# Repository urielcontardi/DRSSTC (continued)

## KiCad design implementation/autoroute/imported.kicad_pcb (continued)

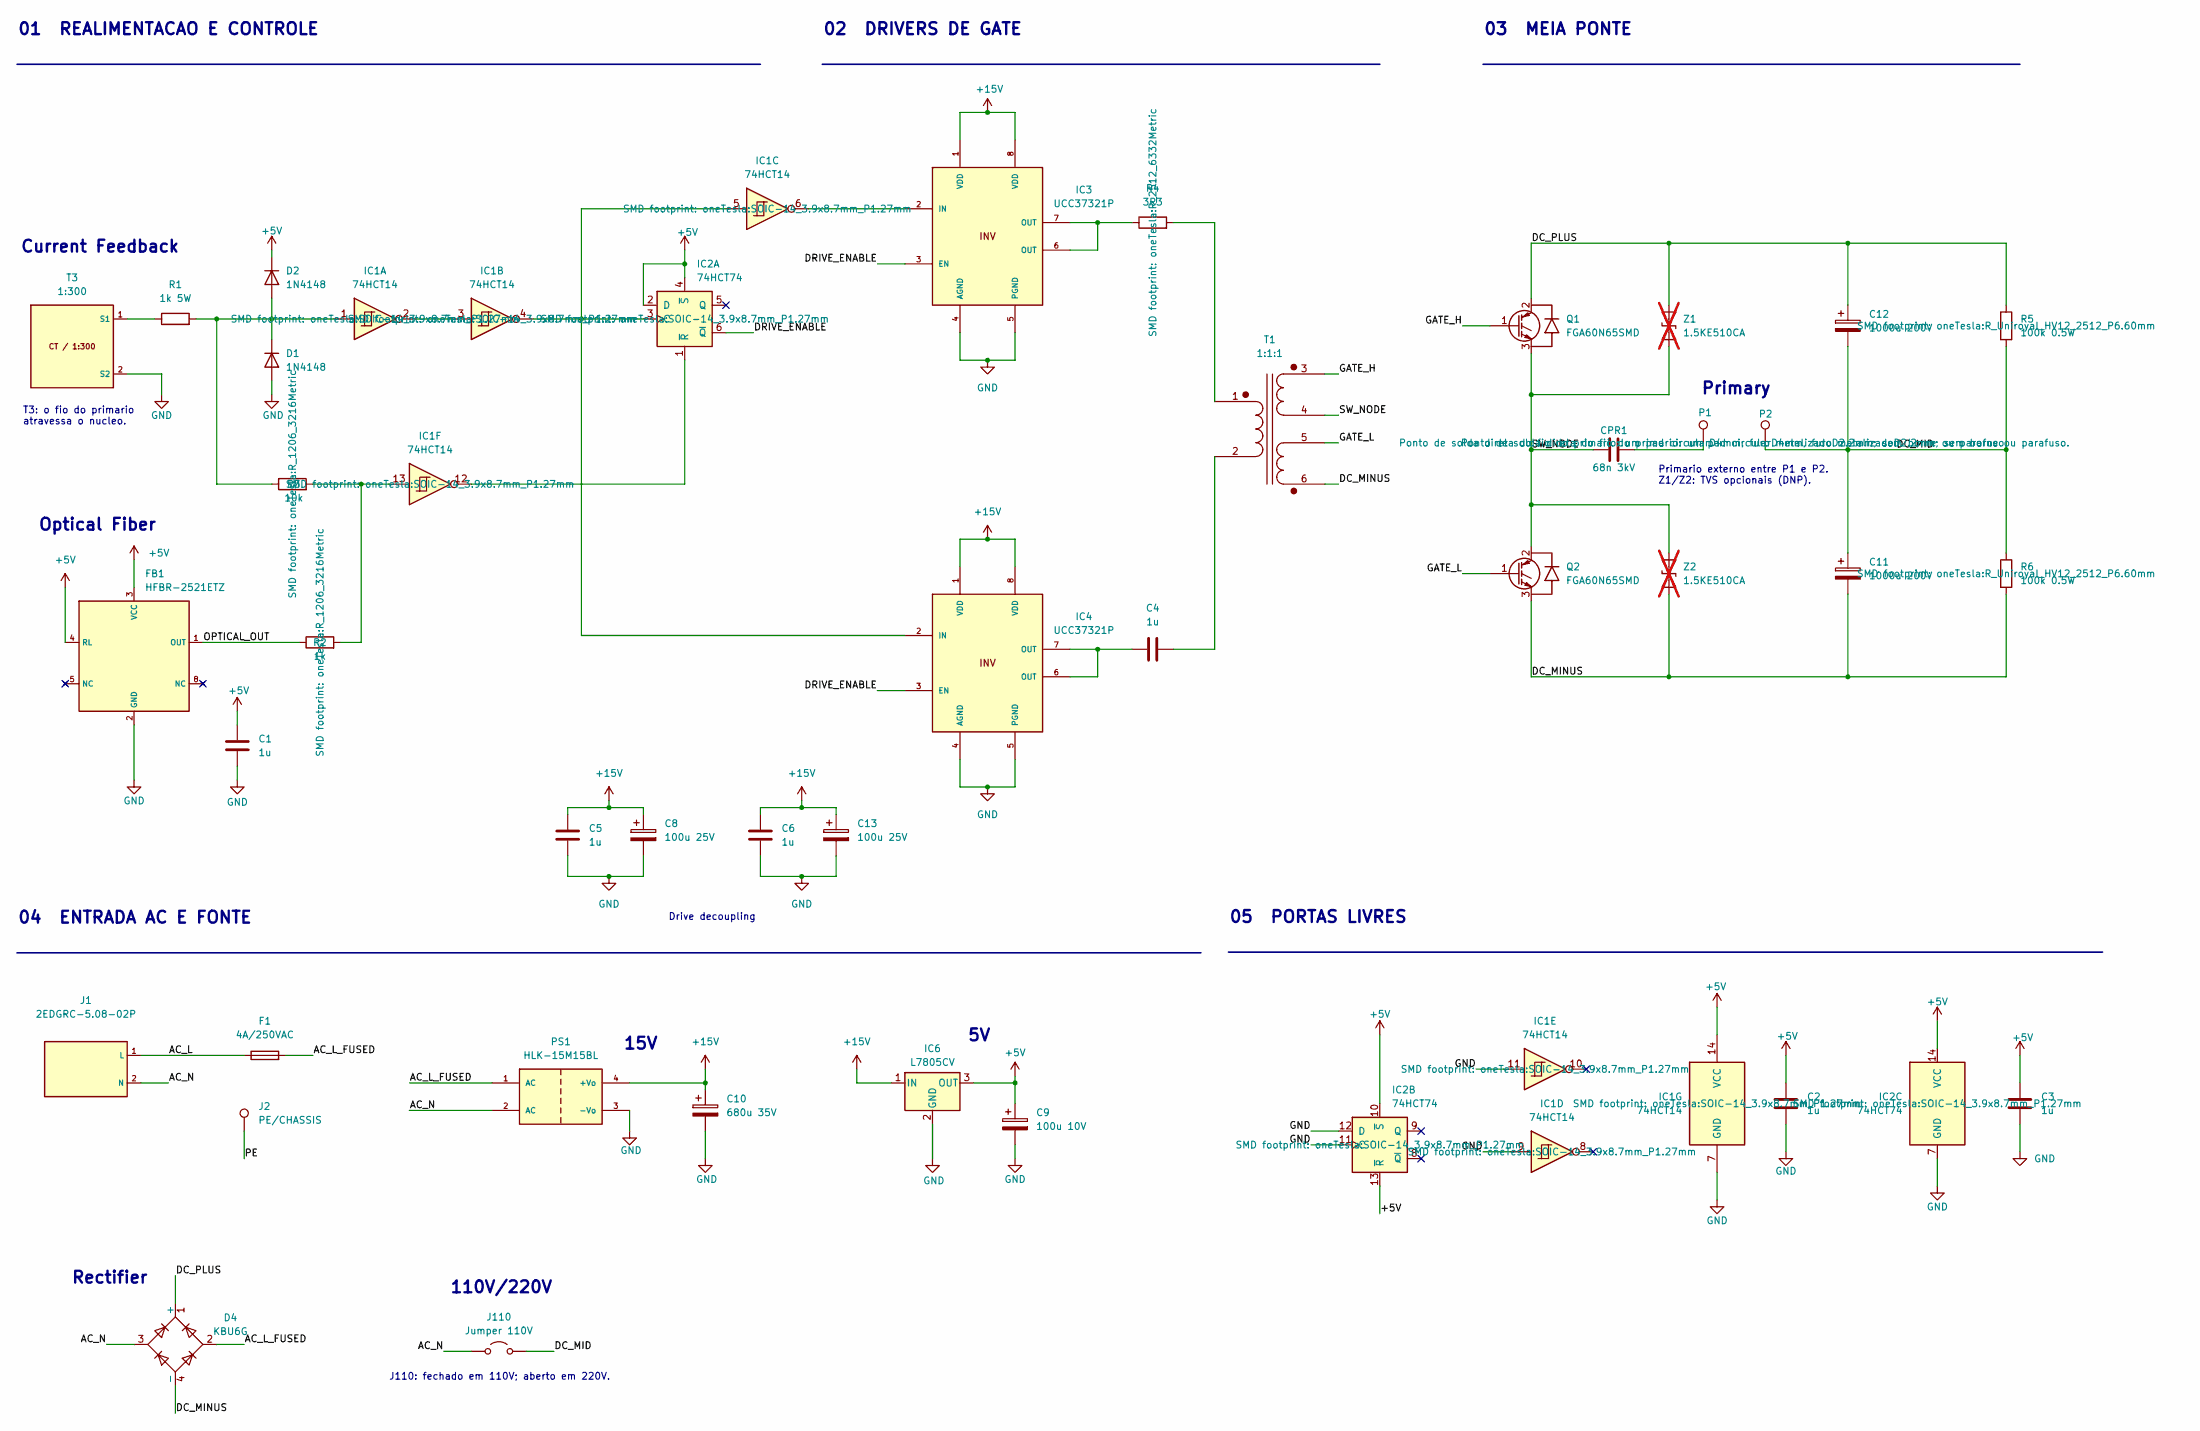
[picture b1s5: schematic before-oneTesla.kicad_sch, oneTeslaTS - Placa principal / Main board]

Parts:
C1, C2, C3, C4, C5, C6: 1u; C_Disc_D7.5mm_W2.5mm_P5.00mm
C8, C13: 100u 25V; CP_D8_P2.54_ReviewPending
C9: 100u 10V; CP_D8_P2.54_ReviewPending
C10: 680u 35V; CP_D12.5_P3.556_ReviewPending
C11, C12: 1000u 200V; CP_D30_P10.16_ReviewPending
CPR1: 68n 3kV; CDE_940C30S68K_F_CONFIRMAR
D1, D2: 1N4148; D_DO-35_SOD27_P7.62mm_Horizontal
D4: KBU6G; Diode_Bridge_Vishay_KBU
F1: 4A/250VAC; Fuseholder_Idall_AS-06_5x20mm_P20.20mm_Horizontal
FB1: HFBR-2521ETZ
IC1: 74HCT14; SOIC-14_3.9x8.7mm_P1.27mm
IC2: 74HCT74; SOIC-14_3.9x8.7mm_P1.27mm
IC3, IC4: UCC37321P; DIP-8_W7.62mm_Socket_LongPads
IC6: L7805CV; TO-220-3_Vertical
J1: 2EDGRC-5.08-02P; TerminalBlock_2EDGRC-5.08_1x02_P5.08mm_Horizontal
J2: PE/CHASSIS; Chassis_PE_M3
J110: Jumper 110V; J110_WireLink_P10.16mm
P1: PRIMARIO A; Primary_WirePad_D4.0mm_Drill2.2mm
P2: PRIMARIO B; Primary_WirePad_D4.0mm_Drill2.2mm
PS1: HLK-15M15BL
Q1, Q2: FGA60N65SMD; Q_TO3P_ImportedPads_ReviewPending
R1: 1k 5W; R_Bourns_PWR8030_20.8x7.6mm_P17.80mm
R2: 1k; R_1206_3216Metric
R3: 10k; R_1206_3216Metric
R4: 3R3; R_2512_6332Metric
R5, R6: 100k 0.5W; R_Uniroyal_HV12_2512_P6.60mm
T1: 1:1:1; GDT_6Pin_CONFIRMAR
T3: 1:300; CT_1_300_P12.70mm_CONFIRMAR
Z1, Z2: 1.5KE510CA; D_DO201AD_P14.732_ReviewPending; not fitted

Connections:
+5V: C1.1, C2.1, C3.1, C9.1, D2.1 (K), FB1.3 (VCC), FB1.4 (RL), IC1.14 (VCC), IC2.2 (D), IC2.4 (~S), IC2.10 (~S), IC2.13 (~R), IC2.14 (VCC), IC6.3 (OUT)
+15V: C5.1, C6.1, C8.1, C10.1, C13.1, IC3.1 (VDD), IC3.8 (VDD), IC4.1 (VDD), IC4.8 (VDD), IC6.1 (IN), PS1.4 (+Vo)
/AC_L: F1.1, J1.1 (L)
/AC_L_FUSED: D4.2, F1.2, PS1.1 (AC)
/AC_N: D4.3, J1.2 (N), J110.1 (A), PS1.2 (AC)
/DC_MID: C11.1, C12.2, J110.2 (B), P2.1 (1_1), R5.2, R6.1
/DC_MINUS: C11.2, D4.4 (-), Q2.3 (E), R6.2, T1.6 (SD), Z2.2 (A2)
/DC_PLUS: C12.1, D4.1 (+), Q1.2 (C), R5.1, Z1.1 (A1)
/DRIVE_ENABLE: IC2.6 (~Q), IC3.3 (EN), IC4.3 (EN)
/GATE_H: Q1.1 (G), T1.3 (SA)
/GATE_L: Q2.1 (G), T1.5 (SC)
/OPTICAL_OUT: FB1.1 (OUT), R2.1
GND: C1.2, C2.2, C3.2, C5.2, C6.2, C8.2, C9.2, C10.2, C13.2, D1.2 (A), FB1.2 (GND), IC1.7 (GND), IC1.9, IC1.11, IC2.7 (GND), IC2.11 (C), IC2.12 (D), IC3.4 (AGND), IC3.5 (PGND), IC4.4 (AGND), IC4.5 (PGND), IC6.2 (GND), J2.1, PS1.3 (-Vo), T3.2 (S2)
unnamed: C4.1, IC4.6 (OUT), IC4.7 (OUT)
unnamed: CPR1.2, P1.1 (1_1)
unnamed: D1.1 (K), D2.2 (A), IC1.1, R1.2, R3.1
unnamed: IC1.2, IC1.3
unnamed: IC1.13, R2.2, R3.2
unnamed: IC1.4, IC1.5, IC2.3 (C), IC4.2 (IN)
unnamed: IC1.12, IC2.1 (~R)
unnamed: IC1.6, IC3.2 (IN)
unnamed: IC3.6 (OUT), IC3.7 (OUT), R4.1
unnamed: R4.2, T1.1 (AA)
unnamed: C4.2, T1.2 (AB)
unnamed: R1.1, T3.1 (S1)

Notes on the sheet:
110V/220V
01 REALIMENTACAO E CONTROLE
03 MEIA PONTE
T3: o fio do primario atravessa o nucleo.
J110: fechado em 110V; aberto em 220V.
04 ENTRADA AC E FONTE
Drive decoupling
Current Feedback
Rectifier
Primario externo entre P1 e P2. Z1/Z2: TVS opcionais (DNP).
15V
02 DRIVERS DE GATE
05 PORTAS LIVRES
Optical Fiber
Primary

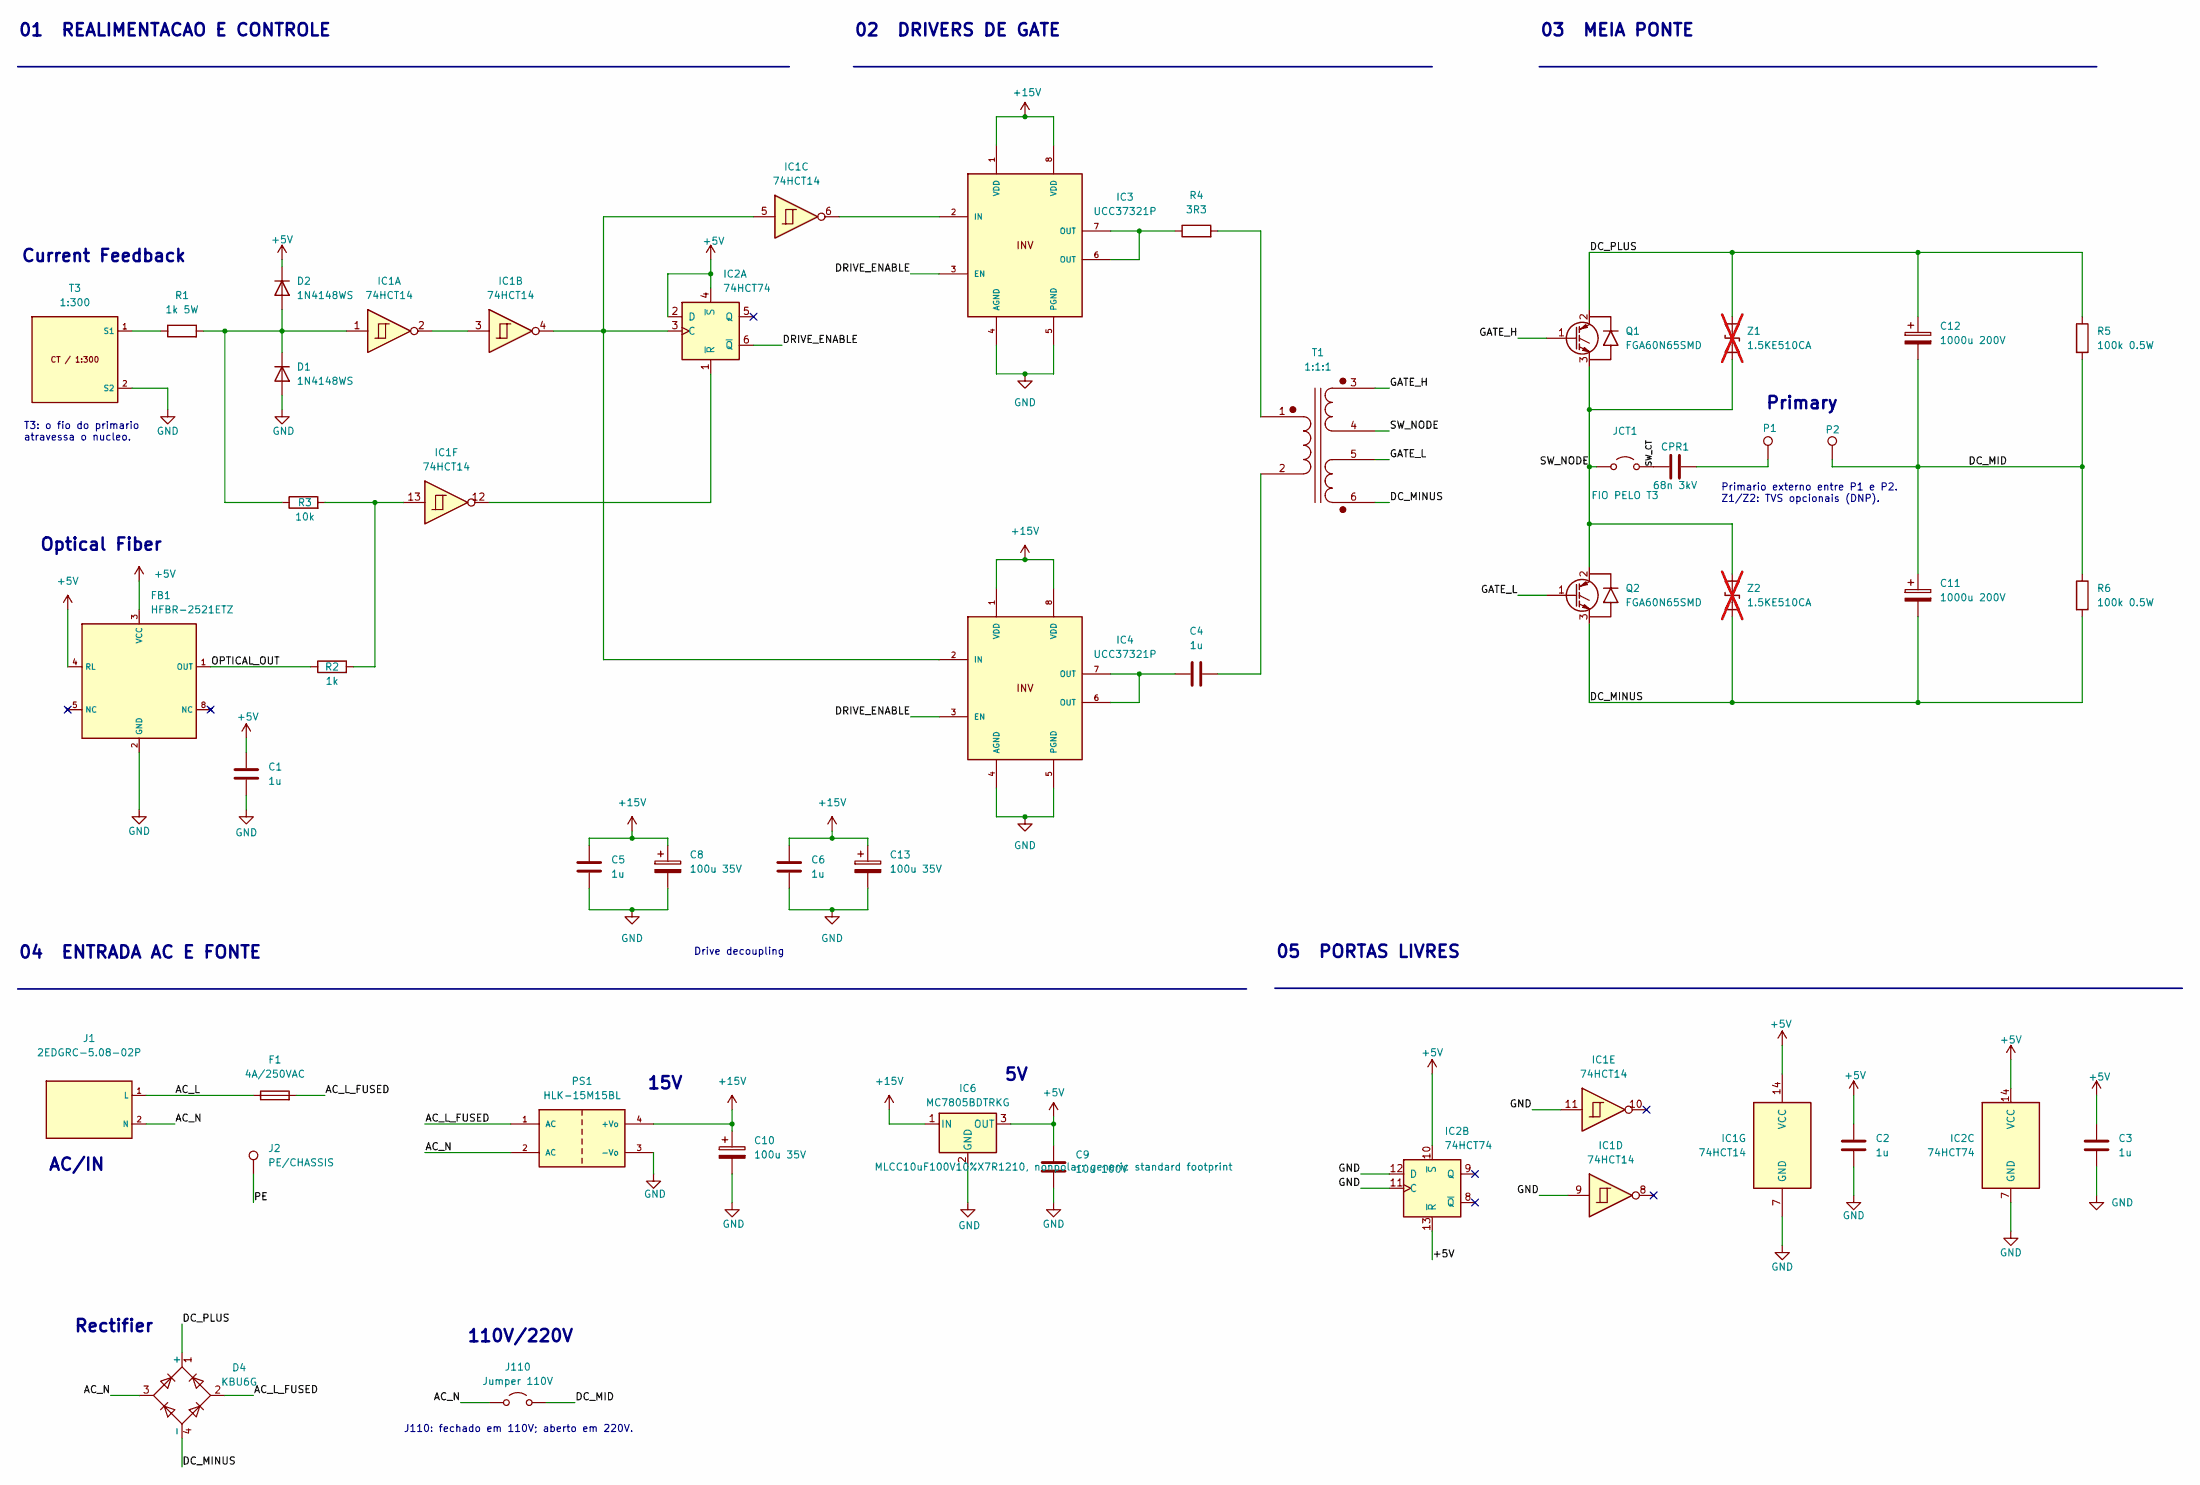
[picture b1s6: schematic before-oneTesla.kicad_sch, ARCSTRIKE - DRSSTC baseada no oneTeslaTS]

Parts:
C1, C2, C3, C5, C6: 1u; C_0805_2012Metric_Pad1.18x1.45mm_HandSolder
C4: 1u; C_Disc_D7.5mm_W2.5mm_P5.00mm
C8, C10, C13: 100u 35V; CP_Elec_8x10
C9: 10u 100V; C_1210_3225Metric
C11, C12: 1000u 200V; CP_D25_H45_P10.16_ReviewPending
CPR1: 68n 3kV; CDE_940C30S68K_F_CONFIRMAR
D1, D2: 1N4148WS; D_SOD-323_HandSoldering
D4: KBU6G; Diode_Bridge_Vishay_KBU
F1: 4A/250VAC; Fuseholder_Idall_AS-06_5x20mm_Slotted_P22.35mm
FB1: HFBR-2521ETZ
IC1: 74HCT14; SOIC-14_3.9x8.7mm_P1.27mm
IC2: 74HCT74; SOIC-14_3.9x8.7mm_P1.27mm
IC3, IC4: UCC37321P; DIP-8_W7.62mm_Socket_LongPads
IC6: MC7805BDTRKG; TO-252-3_TabPin2
J1: 2EDGRC-5.08-02P; TerminalBlock_2EDGRC-5.08_1x02_P5.08mm_Horizontal
J2: PE/CHASSIS; Chassis_PE_M3
J110: Jumper 110V; J110_WireLink_P15.24mm
JCT1: FIO PELO T3; CT_Primary_WireLink_P21.59mm
P1: PRIMARIO A; Primary_WirePad_D4.0mm_Drill2.2mm
P2: PRIMARIO B; Primary_WirePad_D4.0mm_Drill2.2mm
PS1: HLK-15M15BL
Q1, Q2: FGA60N65SMD; Q_TO3P_ImportedPads_ReviewPending
R1: 1k 5W; R_Axial_Vishay_AC05_L18.0mm_D7.5mm_P10.16mm_Vertical
R2: 1k; R_1206_3216Metric
R3: 10k; R_1206_3216Metric
R4: 3R3; R_Axial_DIN0207_L6.3mm_D2.5mm_P7.62mm_Horizontal
R5, R6: 100k 0.5W; R_Uniroyal_HV12_2512_P6.60mm
T1: 1:1:1; GDT_6Pin_CONFIRMAR
T3: 1:300; CT_1_300_P12.70mm_CONFIRMAR
Z1, Z2: 1.5KE510CA; D_DO201AD_P14.732_ReviewPending; not fitted

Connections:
+5V: C1.1, C2.1, C3.1, C9.1, D2.1 (K), FB1.3 (VCC), FB1.4 (RL), IC1.14 (VCC), IC2.2 (D), IC2.4 (~S), IC2.10 (~S), IC2.13 (~R), IC2.14 (VCC), IC6.3 (OUT)
+15V: C5.1, C6.1, C8.1, C10.1, C13.1, IC3.1 (VDD), IC3.8 (VDD), IC4.1 (VDD), IC4.8 (VDD), IC6.1 (IN), PS1.4 (+Vo)
/AC_L: F1.1, J1.1 (L)
/AC_L_FUSED: D4.2, F1.2, PS1.1 (AC)
/AC_N: D4.3, J1.2 (N), J110.1 (A), PS1.2 (AC)
/DC_MID: C11.1, C12.2, J110.2 (B), P2.1 (1_1), R5.2, R6.1
/DC_MINUS: C11.2, D4.4 (-), Q2.3 (E), R6.2, T1.6 (SD), Z2.2 (A2)
/DC_PLUS: C12.1, D4.1 (+), Q1.2 (C), R5.1, Z1.1 (A1)
/DRIVE_ENABLE: IC2.6 (~Q), IC3.3 (EN), IC4.3 (EN)
/GATE_H: Q1.1 (G), T1.3 (SA)
/GATE_L: Q2.1 (G), T1.5 (SC)
/OPTICAL_OUT: FB1.1 (OUT), R2.1
GND: C1.2, C2.2, C3.2, C5.2, C6.2, C8.2, C9.2, C10.2, C13.2, D1.2 (A), FB1.2 (GND), IC1.7 (GND), IC1.9, IC1.11, IC2.7 (GND), IC2.11 (C), IC2.12 (D), IC3.4 (AGND), IC3.5 (PGND), IC4.4 (AGND), IC4.5 (PGND), IC6.2 (GND), J2.1, PS1.3 (-Vo), T3.2 (S2)
unnamed: C4.1, IC4.6 (OUT), IC4.7 (OUT)
unnamed: CPR1.2, P1.1 (1_1)
unnamed: D1.1 (K), D2.2 (A), IC1.1, R1.2, R3.1
unnamed: IC1.2, IC1.3
unnamed: IC1.13, R2.2, R3.2
unnamed: IC1.4, IC1.5, IC2.3 (C), IC4.2 (IN)
unnamed: IC1.12, IC2.1 (~R)
unnamed: IC1.6, IC3.2 (IN)
unnamed: IC3.6 (OUT), IC3.7 (OUT), R4.1
unnamed: R4.2, T1.1 (AA)
unnamed: C4.2, T1.2 (AB)
unnamed: R1.1, T3.1 (S1)

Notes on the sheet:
110V/220V
01 REALIMENTACAO E CONTROLE
03 MEIA PONTE
T3: o fio do primario atravessa o nucleo.
J110: fechado em 110V; aberto em 220V.
04 ENTRADA AC E FONTE
Drive decoupling
Current Feedback
AC/IN
Rectifier
Primario externo entre P1 e P2. Z1/Z2: TVS opcionais (DNP).
15V
02 DRIVERS DE GATE
05 PORTAS LIVRES
Optical Fiber
Primary

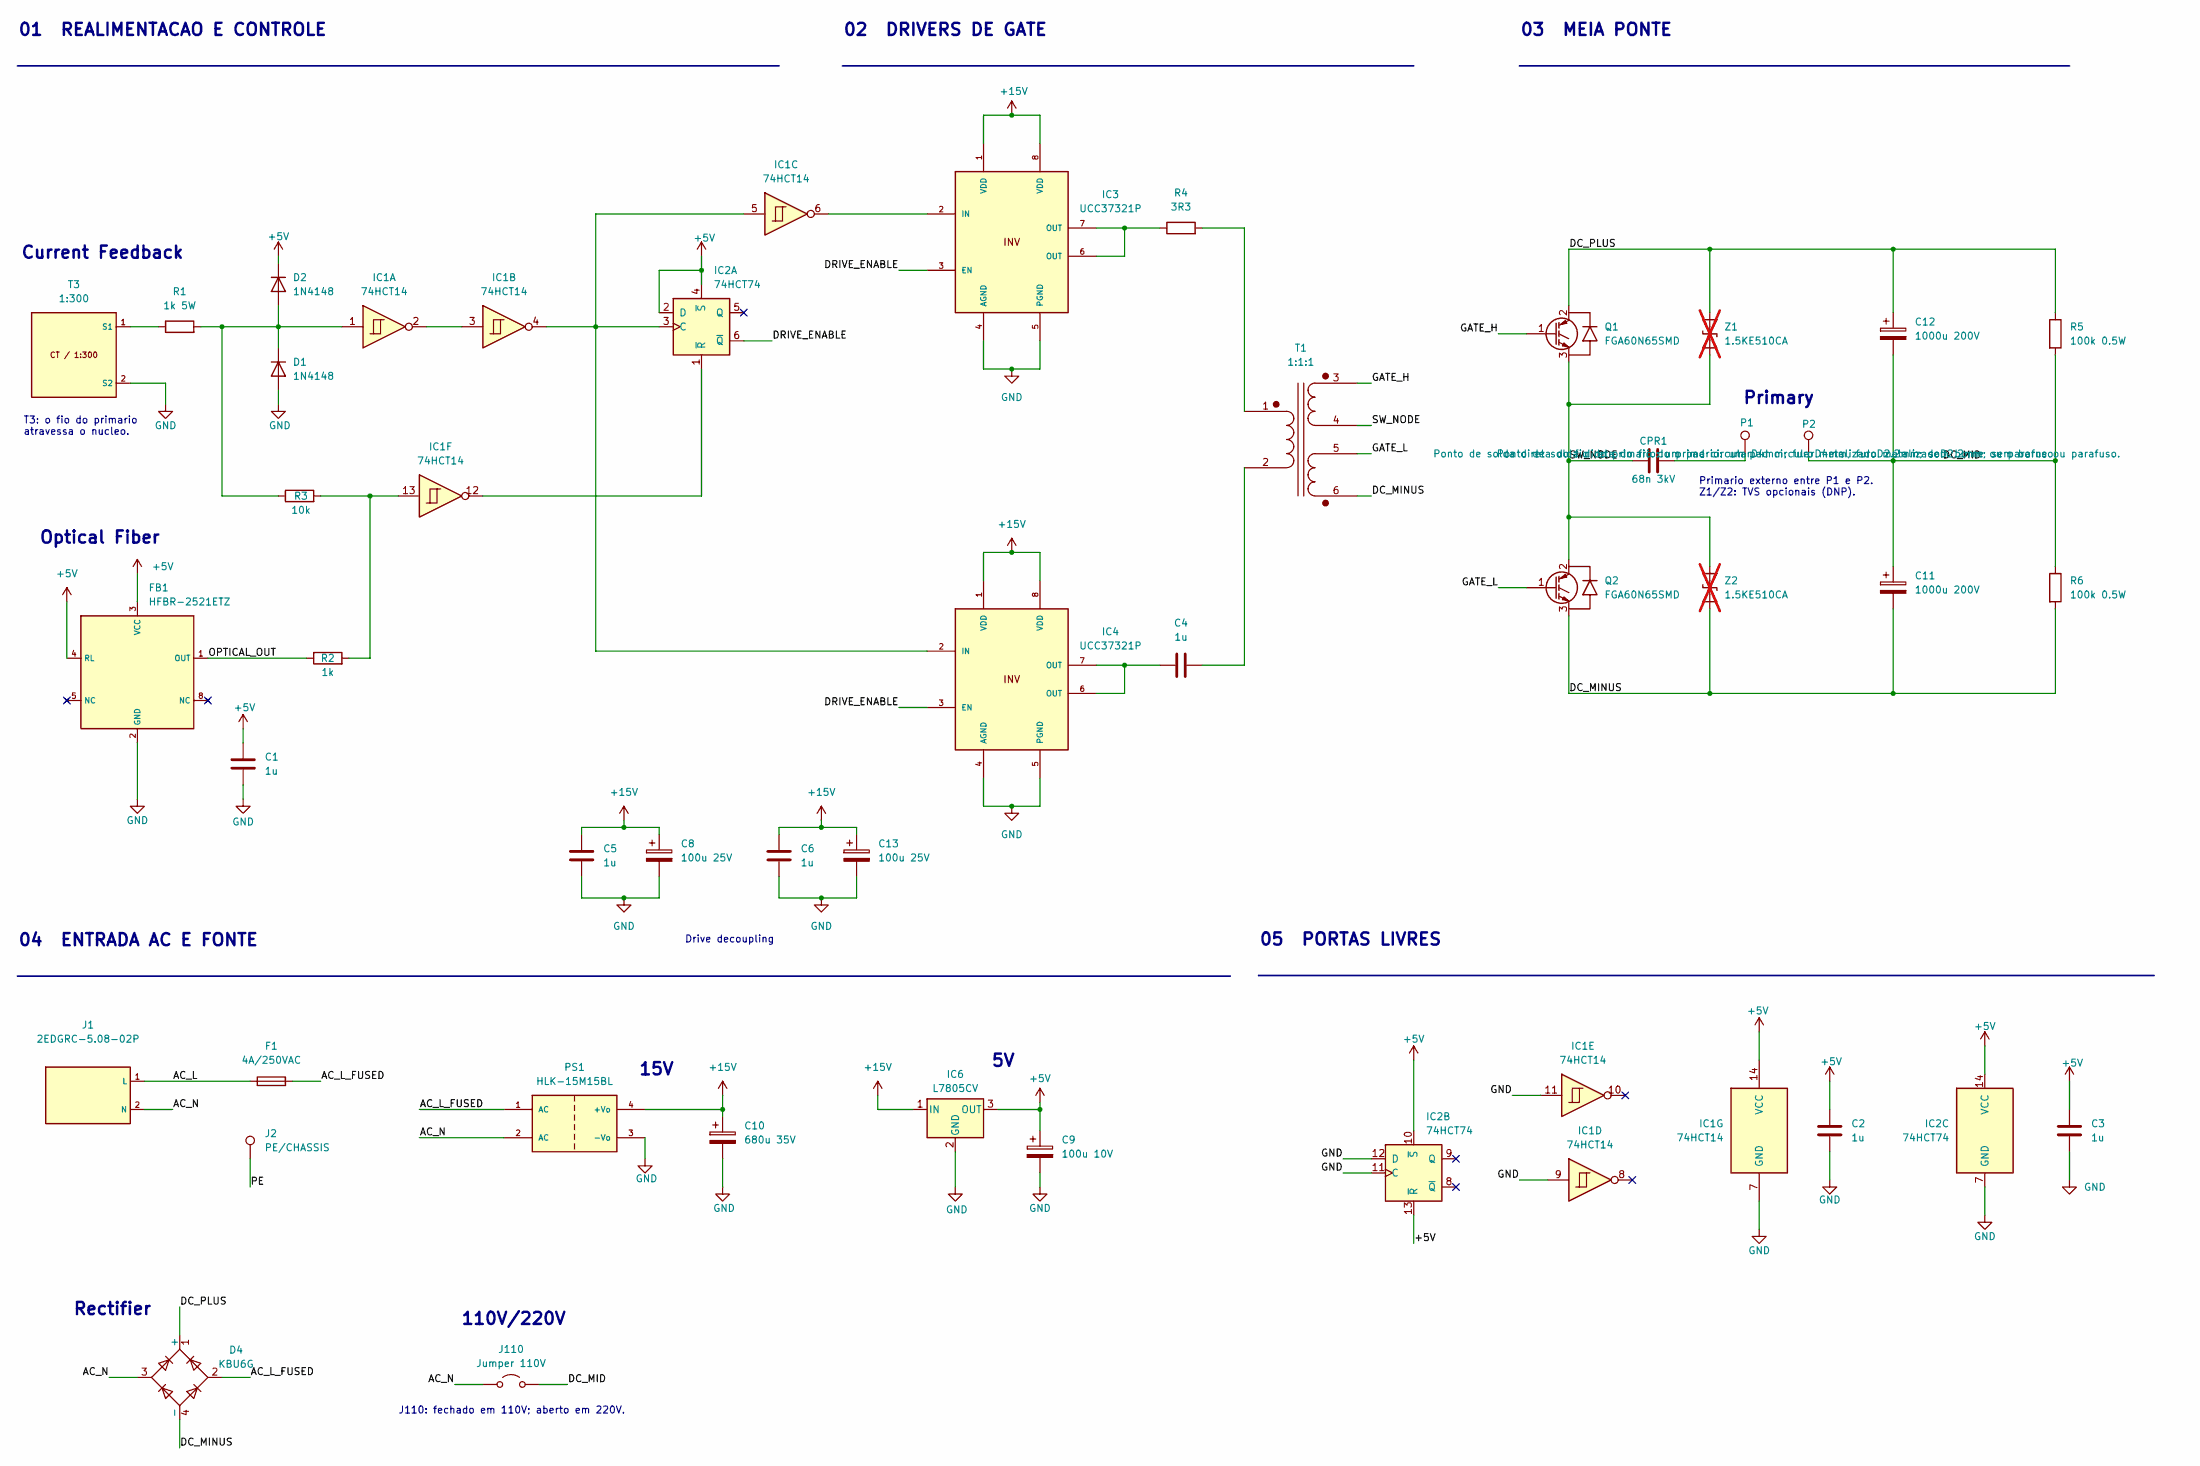
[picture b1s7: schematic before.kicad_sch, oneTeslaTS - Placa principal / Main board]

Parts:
C1, C2, C3, C4, C5, C6: 1u; C_Disc_D7.5mm_W2.5mm_P5.00mm
C8, C13: 100u 25V; CP_D8_P2.54_ReviewPending
C9: 100u 10V; CP_D8_P2.54_ReviewPending
C10: 680u 35V; CP_D12.5_P3.556_ReviewPending
C11, C12: 1000u 200V; CP_D30_P10.16_ReviewPending
CPR1: 68n 3kV; CDE_940C30S68K_F_CONFIRMAR
D1, D2: 1N4148; D_DO-35_SOD27_P7.62mm_Horizontal
D4: KBU6G; Diode_Bridge_Vishay_KBU
F1: 4A/250VAC; Fuseholder_Idall_AS-06_5x20mm_P20.20mm_Horizontal
FB1: HFBR-2521ETZ
IC1: 74HCT14; DIP-14_W7.62mm_Socket_LongPads
IC2: 74HCT74; DIP-14_W7.62mm_Socket_LongPads
IC3, IC4: UCC37321P; DIP-8_W7.62mm_Socket_LongPads
IC6: L7805CV; TO-220-3_Vertical
J1: 2EDGRC-5.08-02P; TerminalBlock_2EDGRC-5.08_1x02_P5.08mm_Horizontal
J2: PE/CHASSIS; Chassis_PE_M3
J110: Jumper 110V; J110_WireLink_P10.16mm
P1: PRIMARIO A; Primary_WirePad_D4.0mm_Drill2.2mm
P2: PRIMARIO B; Primary_WirePad_D4.0mm_Drill2.2mm
PS1: HLK-15M15BL
Q1, Q2: FGA60N65SMD; Q_TO3P_ImportedPads_ReviewPending
R1: 1k 5W; R_Axial_Vishay_AC05_L18.0mm_D7.5mm_P23.40mm_Horizontal
R2: 1k; R_Axial_DIN0207_L6.3mm_D2.5mm_P7.62mm_Horizontal
R3: 10k; R_Axial_DIN0207_L6.3mm_D2.5mm_P7.62mm_Horizontal
R4: 3R3; R_Axial_DIN0207_L6.3mm_D2.5mm_P7.62mm_Horizontal
R5, R6: 100k 0.5W; R_L9_P10.16_ReviewPending
T1: 1:1:1; GDT_6Pin_CONFIRMAR
T3: 1:300; CT_1_300_P12.70mm_CONFIRMAR
Z1, Z2: 1.5KE510CA; D_DO201AD_P14.732_ReviewPending; not fitted

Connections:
+5V: C1.1, C2.1, C3.1, C9.1, D2.1 (K), FB1.3 (VCC), FB1.4 (RL), IC1.14 (VCC), IC2.2 (D), IC2.4 (~S), IC2.10 (~S), IC2.13 (~R), IC2.14 (VCC), IC6.3 (OUT)
+15V: C5.1, C6.1, C8.1, C10.1, C13.1, IC3.1 (VDD), IC3.8 (VDD), IC4.1 (VDD), IC4.8 (VDD), IC6.1 (IN), PS1.4 (+Vo)
/AC_L: F1.1, J1.1 (L)
/AC_L_FUSED: D4.2, F1.2, PS1.1 (AC)
/AC_N: D4.3, J1.2 (N), J110.1 (A), PS1.2 (AC)
/DC_MID: C11.1, C12.2, J110.2 (B), P2.1 (1_1), R5.2, R6.1
/DC_MINUS: C11.2, D4.4 (-), Q2.3 (E), R6.2, T1.6 (SD), Z2.2 (A2)
/DC_PLUS: C12.1, D4.1 (+), Q1.2 (C), R5.1, Z1.1 (A1)
/DRIVE_ENABLE: IC2.6 (~Q), IC3.3 (EN), IC4.3 (EN)
/GATE_H: Q1.1 (G), T1.3 (SA)
/GATE_L: Q2.1 (G), T1.5 (SC)
/OPTICAL_OUT: FB1.1 (OUT), R2.1
GND: C1.2, C2.2, C3.2, C5.2, C6.2, C8.2, C9.2, C10.2, C13.2, D1.2 (A), FB1.2 (GND), IC1.7 (GND), IC1.9, IC1.11, IC2.7 (GND), IC2.11 (C), IC2.12 (D), IC3.4 (AGND), IC3.5 (PGND), IC4.4 (AGND), IC4.5 (PGND), IC6.2 (GND), J2.1, PS1.3 (-Vo), T3.2 (S2)
unnamed: C4.1, IC4.6 (OUT), IC4.7 (OUT)
unnamed: CPR1.2, P1.1 (1_1)
unnamed: D1.1 (K), D2.2 (A), IC1.1, R1.2, R3.1
unnamed: IC1.2, IC1.3
unnamed: IC1.13, R2.2, R3.2
unnamed: IC1.4, IC1.5, IC2.3 (C), IC4.2 (IN)
unnamed: IC1.12, IC2.1 (~R)
unnamed: IC1.6, IC3.2 (IN)
unnamed: IC3.6 (OUT), IC3.7 (OUT), R4.1
unnamed: R4.2, T1.1 (AA)
unnamed: C4.2, T1.2 (AB)
unnamed: R1.1, T3.1 (S1)

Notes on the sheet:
110V/220V
01 REALIMENTACAO E CONTROLE
03 MEIA PONTE
T3: o fio do primario atravessa o nucleo.
J110: fechado em 110V; aberto em 220V.
04 ENTRADA AC E FONTE
Drive decoupling
Current Feedback
Rectifier
Primario externo entre P1 e P2. Z1/Z2: TVS opcionais (DNP).
15V
02 DRIVERS DE GATE
05 PORTAS LIVRES
Optical Fiber
Primary

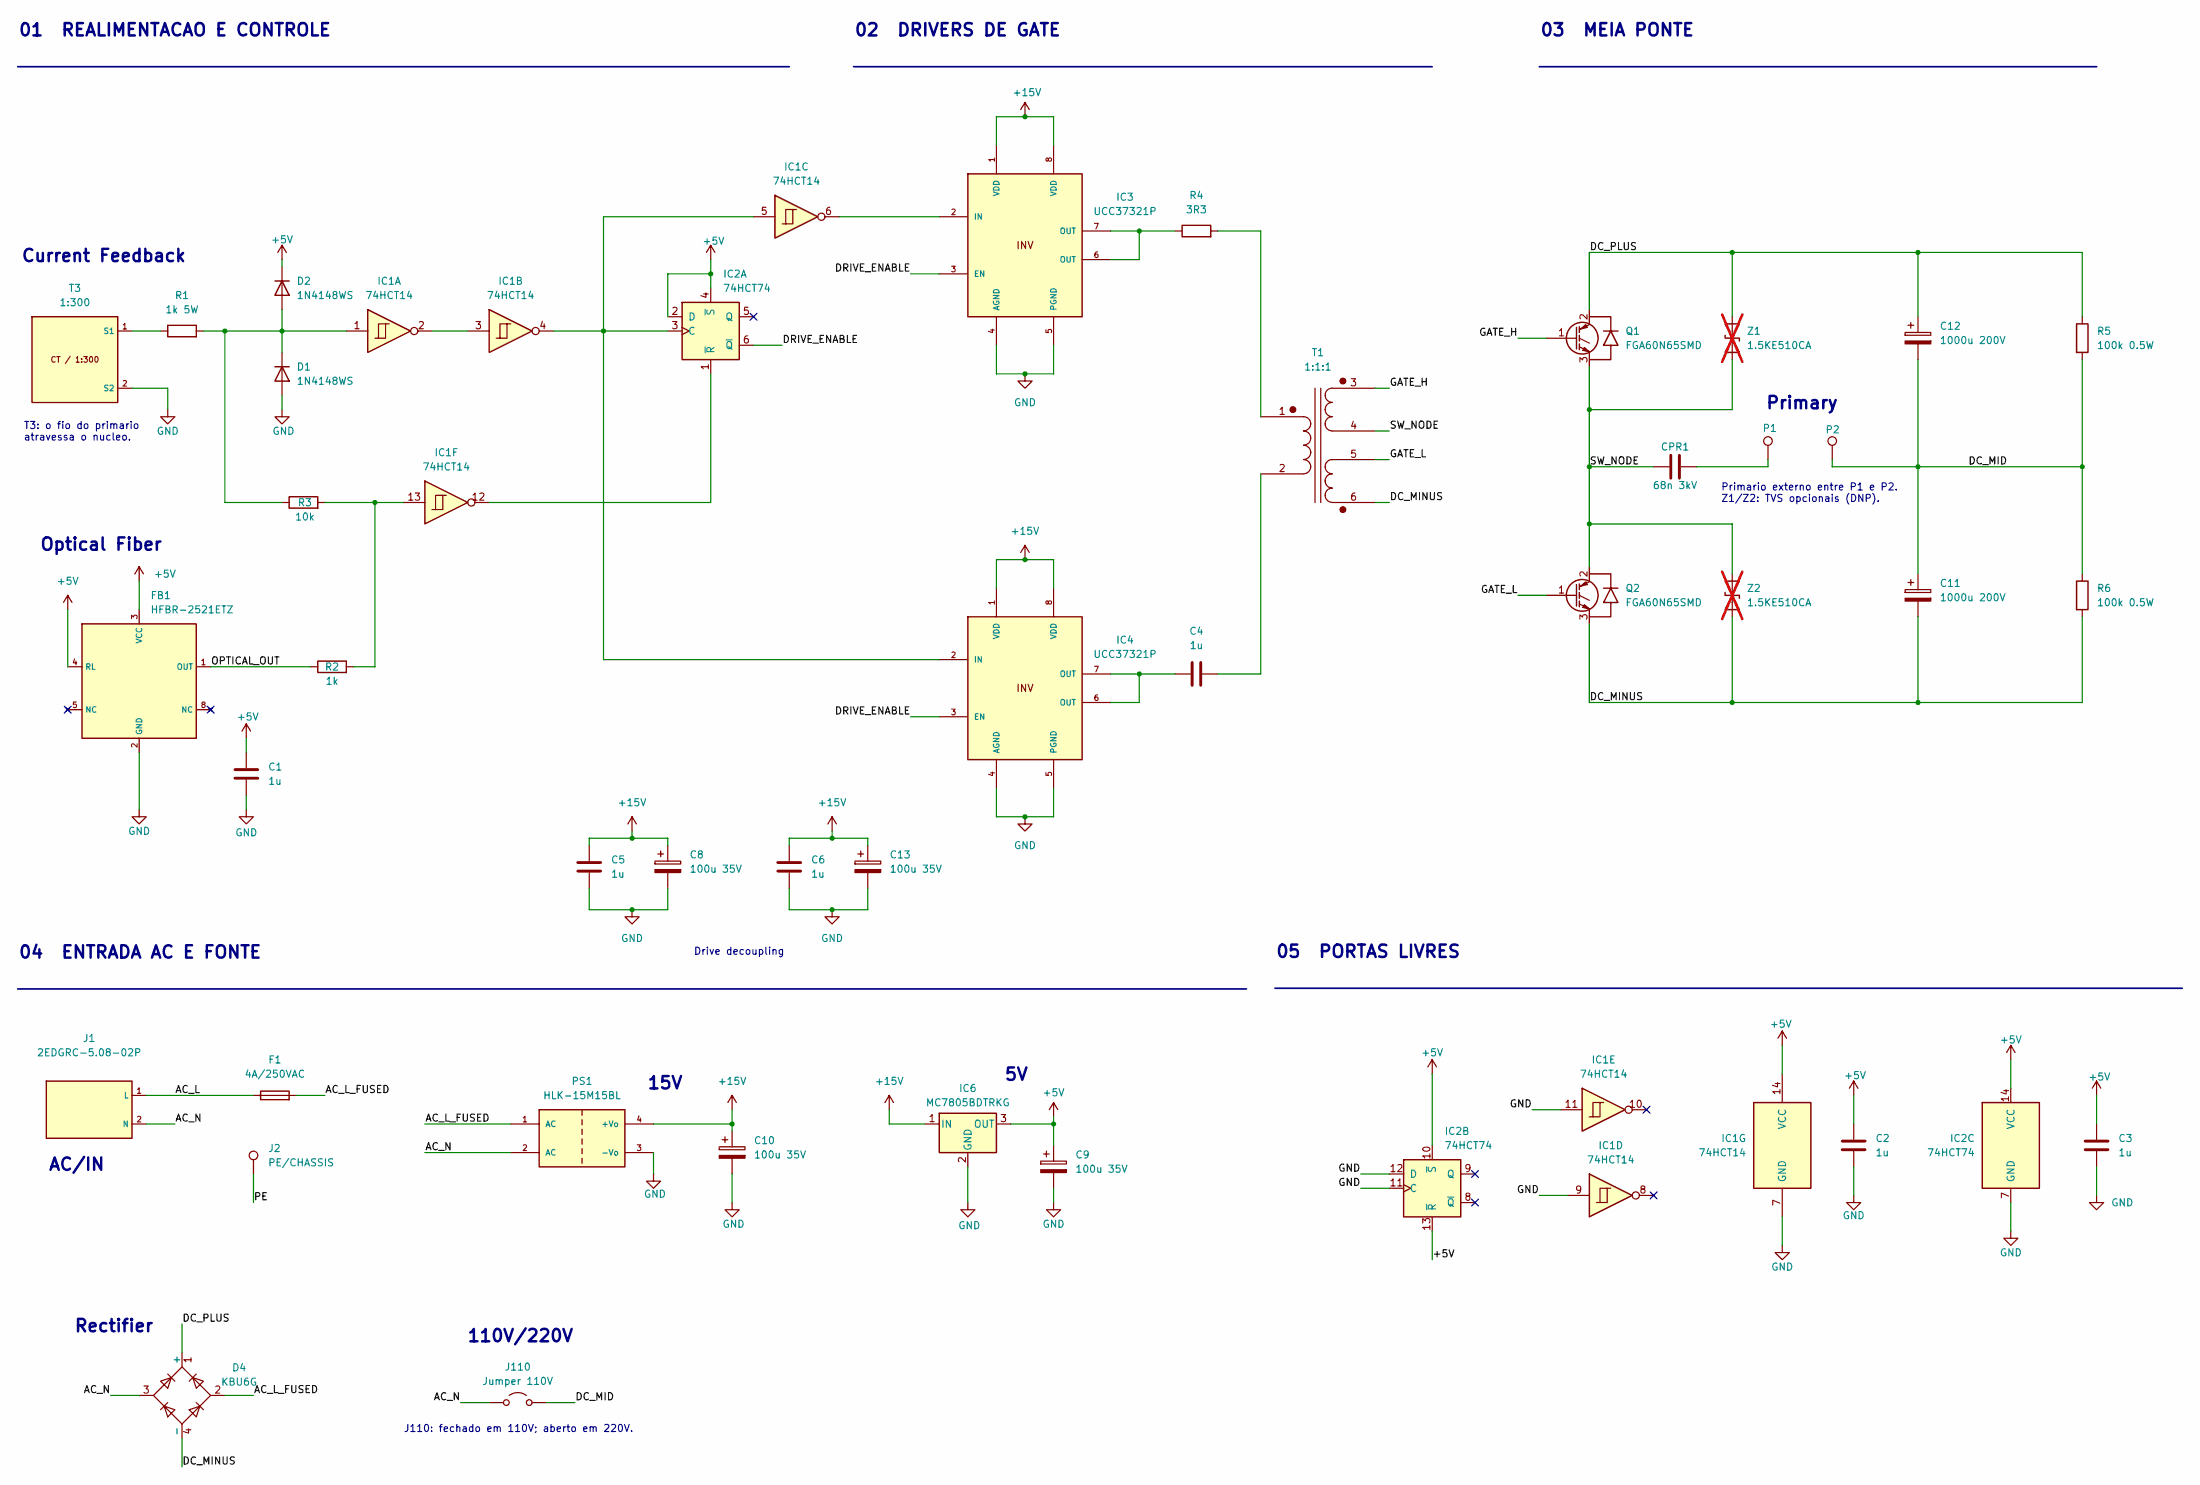
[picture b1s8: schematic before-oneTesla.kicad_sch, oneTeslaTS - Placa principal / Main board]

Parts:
C1, C2, C3, C5, C6: 1u; C_0805_2012Metric_Pad1.18x1.45mm_HandSolder
C4: 1u; C_Disc_D7.5mm_W2.5mm_P5.00mm
C8, C9, C10, C13: 100u 35V; CP_Elec_8x10
C11, C12: 1000u 200V; CP_D25_H45_P10.16_ReviewPending
CPR1: 68n 3kV; CDE_940C30S68K_F_CONFIRMAR
D1, D2: 1N4148WS; D_SOD-323_HandSoldering
D4: KBU6G; Diode_Bridge_Vishay_KBU
F1: 4A/250VAC; Fuseholder_Idall_AS-06_5x20mm_P20.20mm_Horizontal
FB1: HFBR-2521ETZ
IC1: 74HCT14; SOIC-14_3.9x8.7mm_P1.27mm
IC2: 74HCT74; SOIC-14_3.9x8.7mm_P1.27mm
IC3, IC4: UCC37321P; DIP-8_W7.62mm_Socket_LongPads
IC6: MC7805BDTRKG; TO-252-3_TabPin2
J1: 2EDGRC-5.08-02P; TerminalBlock_2EDGRC-5.08_1x02_P5.08mm_Horizontal
J2: PE/CHASSIS; Chassis_PE_M3
J110: Jumper 110V; J110_WireLink_P10.16mm
P1: PRIMARIO A; Primary_WirePad_D4.0mm_Drill2.2mm
P2: PRIMARIO B; Primary_WirePad_D4.0mm_Drill2.2mm
PS1: HLK-15M15BL
Q1, Q2: FGA60N65SMD; Q_TO3P_ImportedPads_ReviewPending
R1: 1k 5W; R_Axial_Vishay_AC05_L18.0mm_D7.5mm_P10.16mm_Vertical
R2: 1k; R_1206_3216Metric
R3: 10k; R_1206_3216Metric
R4: 3R3; R_Axial_DIN0207_L6.3mm_D2.5mm_P7.62mm_Horizontal
R5, R6: 100k 0.5W; R_Axial_DIN0309_L9.0mm_D3.2mm_P5.08mm_Vertical
T1: 1:1:1; GDT_6Pin_CONFIRMAR
T3: 1:300; CT_1_300_P12.70mm_CONFIRMAR
Z1, Z2: 1.5KE510CA; D_DO201AD_P14.732_ReviewPending; not fitted

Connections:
+5V: C1.1, C2.1, C3.1, C9.1, D2.1 (K), FB1.3 (VCC), FB1.4 (RL), IC1.14 (VCC), IC2.2 (D), IC2.4 (~S), IC2.10 (~S), IC2.13 (~R), IC2.14 (VCC), IC6.3 (OUT)
+15V: C5.1, C6.1, C8.1, C10.1, C13.1, IC3.1 (VDD), IC3.8 (VDD), IC4.1 (VDD), IC4.8 (VDD), IC6.1 (IN), PS1.4 (+Vo)
/AC_L: F1.1, J1.1 (L)
/AC_L_FUSED: D4.2, F1.2, PS1.1 (AC)
/AC_N: D4.3, J1.2 (N), J110.1 (A), PS1.2 (AC)
/DC_MID: C11.1, C12.2, J110.2 (B), P2.1 (1_1), R5.2, R6.1
/DC_MINUS: C11.2, D4.4 (-), Q2.3 (E), R6.2, T1.6 (SD), Z2.2 (A2)
/DC_PLUS: C12.1, D4.1 (+), Q1.2 (C), R5.1, Z1.1 (A1)
/DRIVE_ENABLE: IC2.6 (~Q), IC3.3 (EN), IC4.3 (EN)
/GATE_H: Q1.1 (G), T1.3 (SA)
/GATE_L: Q2.1 (G), T1.5 (SC)
/OPTICAL_OUT: FB1.1 (OUT), R2.1
GND: C1.2, C2.2, C3.2, C5.2, C6.2, C8.2, C9.2, C10.2, C13.2, D1.2 (A), FB1.2 (GND), IC1.7 (GND), IC1.9, IC1.11, IC2.7 (GND), IC2.11 (C), IC2.12 (D), IC3.4 (AGND), IC3.5 (PGND), IC4.4 (AGND), IC4.5 (PGND), IC6.2 (GND), J2.1, PS1.3 (-Vo), T3.2 (S2)
unnamed: C4.1, IC4.6 (OUT), IC4.7 (OUT)
unnamed: CPR1.2, P1.1 (1_1)
unnamed: D1.1 (K), D2.2 (A), IC1.1, R1.2, R3.1
unnamed: IC1.2, IC1.3
unnamed: IC1.13, R2.2, R3.2
unnamed: IC1.4, IC1.5, IC2.3 (C), IC4.2 (IN)
unnamed: IC1.12, IC2.1 (~R)
unnamed: IC1.6, IC3.2 (IN)
unnamed: IC3.6 (OUT), IC3.7 (OUT), R4.1
unnamed: R4.2, T1.1 (AA)
unnamed: C4.2, T1.2 (AB)
unnamed: R1.1, T3.1 (S1)

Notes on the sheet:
110V/220V
01 REALIMENTACAO E CONTROLE
03 MEIA PONTE
T3: o fio do primario atravessa o nucleo.
J110: fechado em 110V; aberto em 220V.
04 ENTRADA AC E FONTE
Drive decoupling
Current Feedback
AC/IN
Rectifier
Primario externo entre P1 e P2. Z1/Z2: TVS opcionais (DNP).
15V
02 DRIVERS DE GATE
05 PORTAS LIVRES
Optical Fiber
Primary

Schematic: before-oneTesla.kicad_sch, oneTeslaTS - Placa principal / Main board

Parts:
C1, C2, C3, C5, C6: 1u; C_0805_2012Metric_Pad1.18x1.45mm_HandSolder
C4: 1u; C_Disc_D7.5mm_W2.5mm_P5.00mm
C8, C9, C10, C13: 100u 35V; CP_Elec_8x10
C11, C12: 1000u 200V; CP_D25_H45_P10.16_ReviewPending
CPR1: 68n 3kV; CDE_940C30S68K_F_CONFIRMAR
D1, D2: 1N4148WS; D_SOD-323_HandSoldering
D4: KBU6G; Diode_Bridge_Vishay_KBU
F1: 4A/250VAC; Fuseholder_Idall_AS-06_5x20mm_P20.20mm_Horizontal
FB1: HFBR-2521ETZ
IC1: 74HCT14; SOIC-14_3.9x8.7mm_P1.27mm
IC2: 74HCT74; SOIC-14_3.9x8.7mm_P1.27mm
IC3, IC4: UCC37321P; DIP-8_W7.62mm_Socket_LongPads
IC6: MC7805BDTRKG; TO-252-3_TabPin2
J1: 2EDGRC-5.08-02P; TerminalBlock_2EDGRC-5.08_1x02_P5.08mm_Horizontal
J2: PE/CHASSIS; Chassis_PE_M3
J110: Jumper 110V; J110_WireLink_P10.16mm
P1: PRIMARIO A; Primary_WirePad_D4.0mm_Drill2.2mm
P2: PRIMARIO B; Primary_WirePad_D4.0mm_Drill2.2mm
PS1: HLK-15M15BL
Q1, Q2: FGA60N65SMD; Q_TO3P_ImportedPads_ReviewPending
R1: 1k 5W; R_Axial_Vishay_AC05_L18.0mm_D7.5mm_P10.16mm_Vertical
R2: 1k; R_1206_3216Metric
R3: 10k; R_1206_3216Metric
R4: 3R3; R_Axial_DIN0207_L6.3mm_D2.5mm_P7.62mm_Horizontal
R5, R6: 100k 0.5W; R_Uniroyal_HV12_2512_P6.60mm
T1: 1:1:1; GDT_6Pin_CONFIRMAR
T3: 1:300; CT_1_300_P12.70mm_CONFIRMAR
Z1, Z2: 1.5KE510CA; D_DO201AD_P14.732_ReviewPending; not fitted

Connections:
+5V: C1.1, C2.1, C3.1, C9.1, D2.1 (K), FB1.3 (VCC), FB1.4 (RL), IC1.14 (VCC), IC2.2 (D), IC2.4 (~S), IC2.10 (~S), IC2.13 (~R), IC2.14 (VCC), IC6.3 (OUT)
+15V: C5.1, C6.1, C8.1, C10.1, C13.1, IC3.1 (VDD), IC3.8 (VDD), IC4.1 (VDD), IC4.8 (VDD), IC6.1 (IN), PS1.4 (+Vo)
/AC_L: F1.1, J1.1 (L)
/AC_L_FUSED: D4.2, F1.2, PS1.1 (AC)
/AC_N: D4.3, J1.2 (N), J110.1 (A), PS1.2 (AC)
/DC_MID: C11.1, C12.2, J110.2 (B), P2.1 (1_1), R5.2, R6.1
/DC_MINUS: C11.2, D4.4 (-), Q2.3 (E), R6.2, T1.6 (SD), Z2.2 (A2)
/DC_PLUS: C12.1, D4.1 (+), Q1.2 (C), R5.1, Z1.1 (A1)
/DRIVE_ENABLE: IC2.6 (~Q), IC3.3 (EN), IC4.3 (EN)
/GATE_H: Q1.1 (G), T1.3 (SA)
/GATE_L: Q2.1 (G), T1.5 (SC)
/OPTICAL_OUT: FB1.1 (OUT), R2.1
GND: C1.2, C2.2, C3.2, C5.2, C6.2, C8.2, C9.2, C10.2, C13.2, D1.2 (A), FB1.2 (GND), IC1.7 (GND), IC1.9, IC1.11, IC2.7 (GND), IC2.11 (C), IC2.12 (D), IC3.4 (AGND), IC3.5 (PGND), IC4.4 (AGND), IC4.5 (PGND), IC6.2 (GND), J2.1, PS1.3 (-Vo), T3.2 (S2)
unnamed: C4.1, IC4.6 (OUT), IC4.7 (OUT)
unnamed: CPR1.2, P1.1 (1_1)
unnamed: D1.1 (K), D2.2 (A), IC1.1, R1.2, R3.1
unnamed: IC1.2, IC1.3
unnamed: IC1.13, R2.2, R3.2
unnamed: IC1.4, IC1.5, IC2.3 (C), IC4.2 (IN)
unnamed: IC1.12, IC2.1 (~R)
unnamed: IC1.6, IC3.2 (IN)
unnamed: IC3.6 (OUT), IC3.7 (OUT), R4.1
unnamed: R4.2, T1.1 (AA)
unnamed: C4.2, T1.2 (AB)
unnamed: R1.1, T3.1 (S1)

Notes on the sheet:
110V/220V
01 REALIMENTACAO E CONTROLE
03 MEIA PONTE
T3: o fio do primario atravessa o nucleo.
J110: fechado em 110V; aberto em 220V.
04 ENTRADA AC E FONTE
Drive decoupling
Current Feedback
Rectifier
Primario externo entre P1 e P2. Z1/Z2: TVS opcionais (DNP).
15V
02 DRIVERS DE GATE
05 PORTAS LIVRES
Optical Fiber
Primary

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
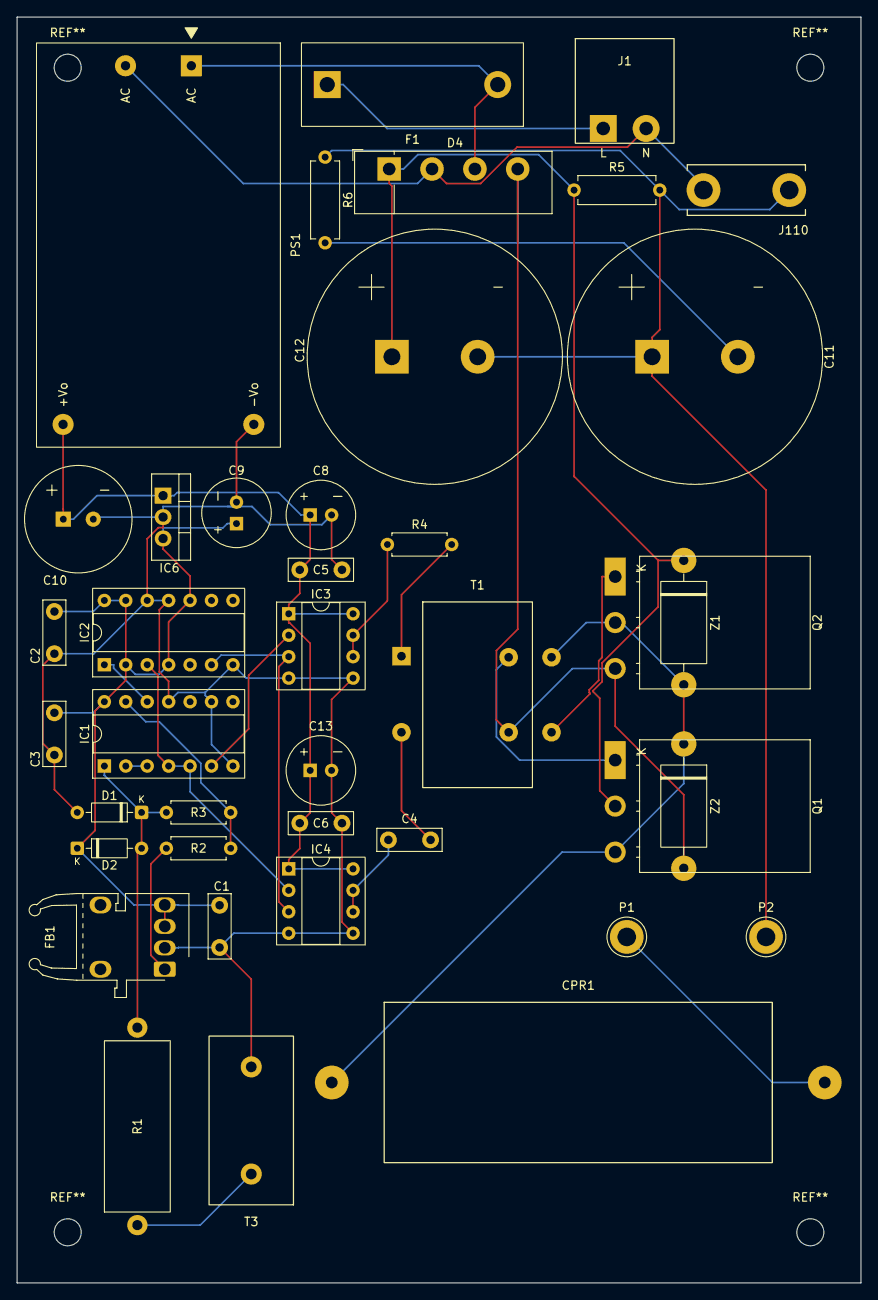
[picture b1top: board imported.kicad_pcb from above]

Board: 2 copper layers, 100.0 x 150.0 mm, 40 parts (0 on the bottom side), 26 nets.
